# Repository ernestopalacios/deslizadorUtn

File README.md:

DeslizadorUtn
=============

Repositorio para el deslizador lineal desarrollado para la Universidad Técnica del Norte.

Manual de ayuda: https://github.com/ernestopalacios/deslizadorUtn/wiki

El reposito esta dividido en las siguientes carpetas:

---> deslizador :  Archivos del deslizador en SolidWorks 2013

---> deslizadorlineal : Documentación del trabajo de grado.

---> labview : Libreria para el control del servomotor en LABVIEW.

---> mbed : Documentacion microcontrolador.

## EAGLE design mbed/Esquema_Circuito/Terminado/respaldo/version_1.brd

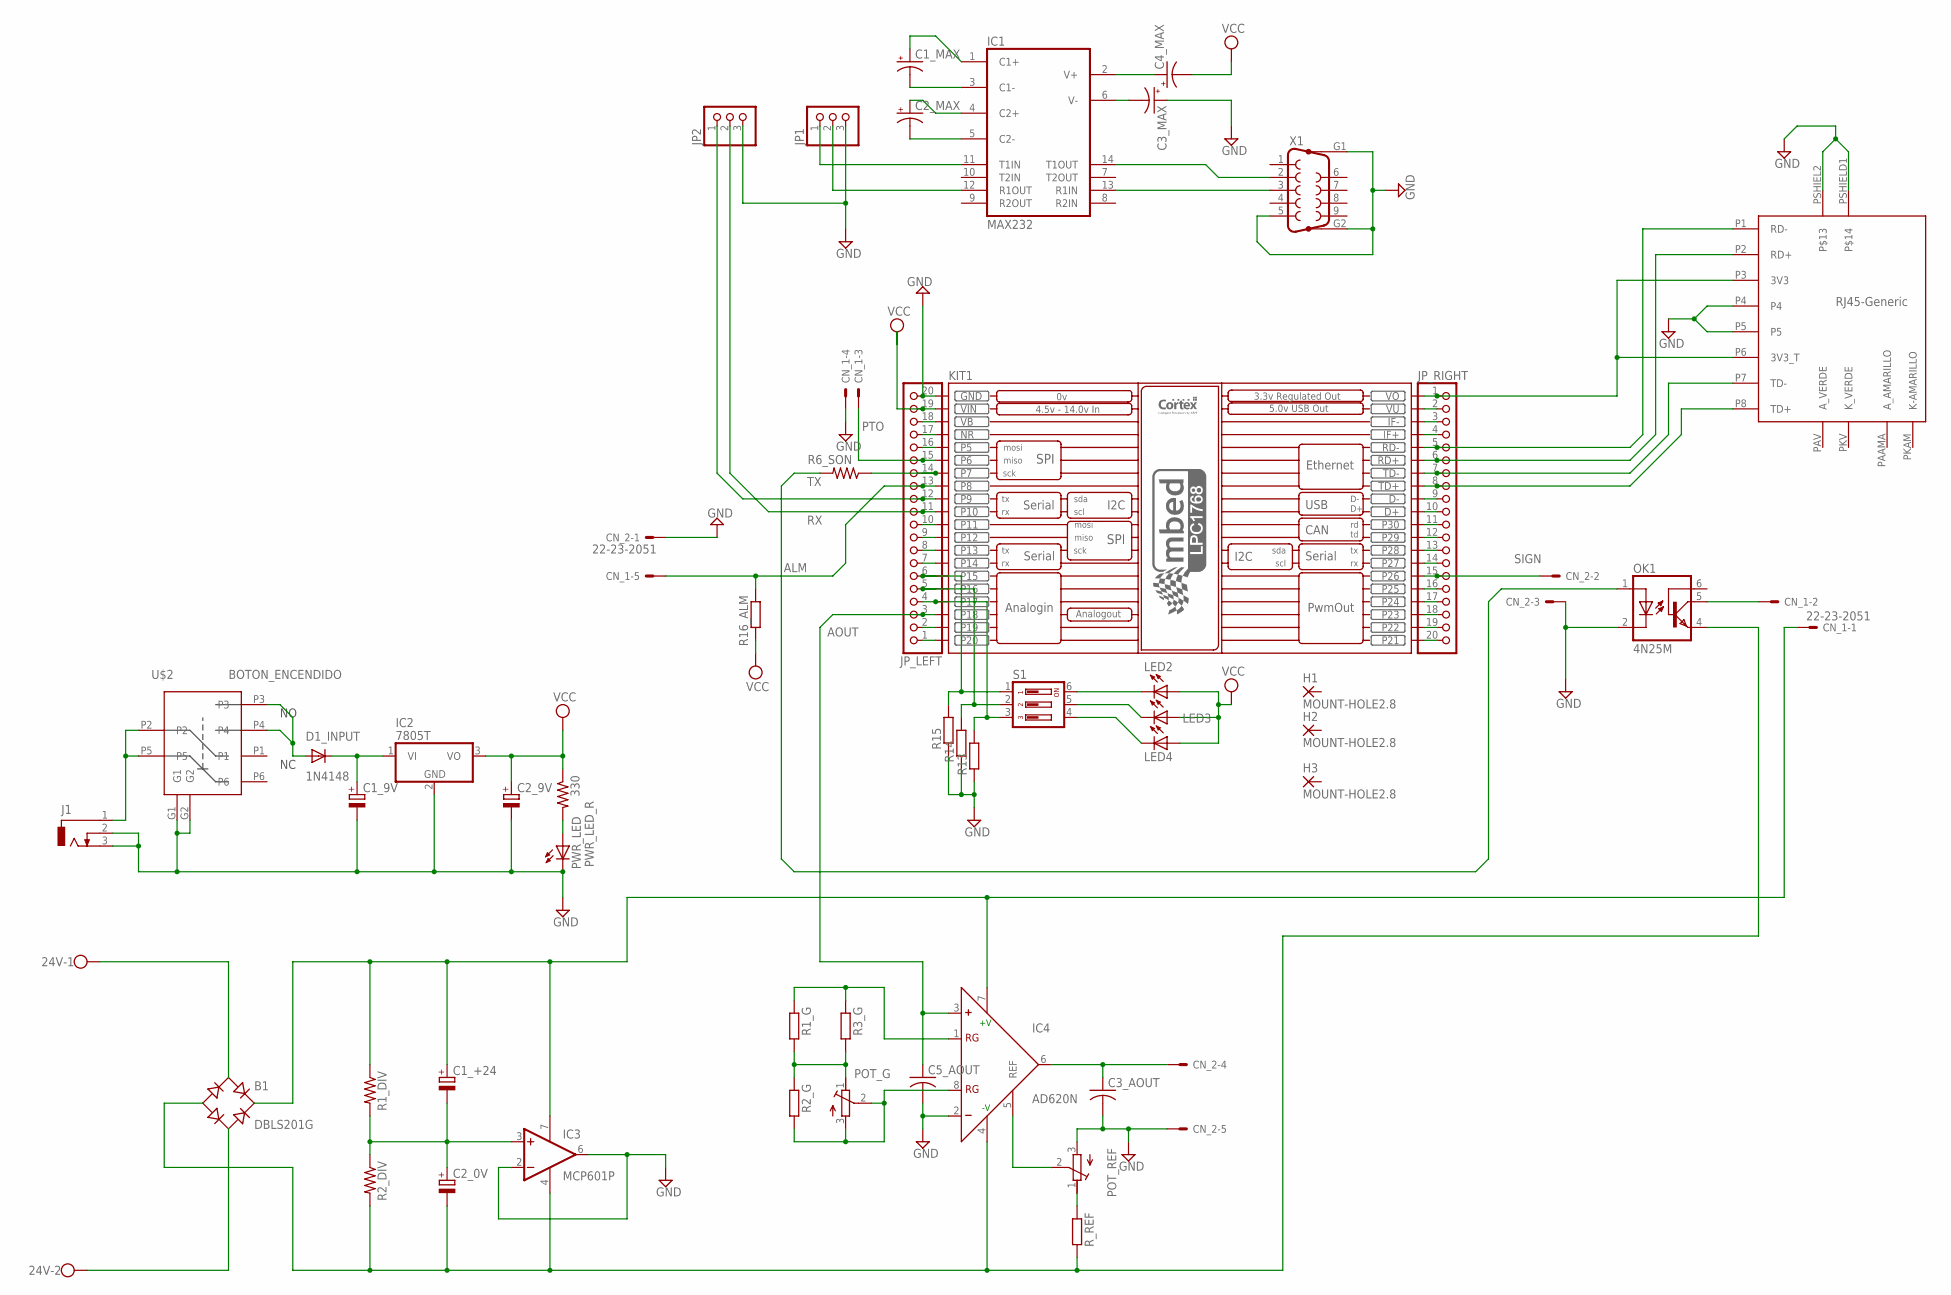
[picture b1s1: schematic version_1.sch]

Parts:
24V: W237-02P; W237-132
B1: DBLS201G; DBS
C1_9V, C1_+24, C2_0V, C2_9V: CPOL-EUTT5D7; TT5D7
C1_MAX, C2_MAX, C3_MAX, C4_MAX: CPOL-USE2,5-6E; E2,5-6E
C3_AOUT, C5_AOUT: C-US025-024X044; C025-024X044
CN_1, CN_2: 22-23-2051
D1_INPUT: 1N4148; DO35-10
H1, H2, H3: MOUNT-HOLE2.8; 2,54/0,8
IC1: MAX232; DIL16
IC2: 7805T; TO220H
IC3: MCP601P; DIL08
IC4: AD620N; DIL08
J1: DCJ0303
JP1, JP2: PINHD-1X3; 1X03
JP_LEFT: PINHD-1X20; 1X20
JP_RIGHT: PINHD-1X20; 1X20
KIT1: MBED_NXP_LPC1768; MBED-KIT
LED2, LED3, LED4: LED3MM
OK1: 4N25M; DIL06
POT_G: R-TRIMMT93XB; RTRIMT93XB
POT_REF: R-TRIMMT93XB; RTRIMT93XB
PWR_LED: LED3MM
PWR_LED_R: 330; 0207/15
R1_DIV, R2_DIV: R-US_0207/10; 0207/10
R1_G, R2_G, R3_G: R-EU_0207/2V; 0207/2V
R6_SON: R-US_0207/7; 0207/7
R13, R14, R15: R-EU_0207/15; 0207/15
R16_ALM: R-EU_0207/12; 0207/12
R_REF: R-EU_0207/2V; 0207/2V
S1: DIP03YL
U$1: RJ-45-GENERIC; RJ45-GENERIC
U$2: BOTON_ENCENDIDO; BOTON_ENCNEDIDO
X1: F09HP

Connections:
ALM: CN_1.5, JP_LEFT.13, KIT1.P$8 (P8), R16_ALM.1
AOUT: C5_AOUT.1, IC4.3 (+), JP_LEFT.3, KIT1.P$18 (P18)
GND: C1_9V.-, C2_9V.-, C3_AOUT.2, C3_MAX.+, C5_AOUT.2, CN_1.4, CN_2.1, CN_2.3, CN_2.5, IC1.15 (GND), IC2.2 (GND), IC3.2 (-IN), IC3.6 (OUT), IC4.2 (-), J1.2, J1.3, JP1.3, JP2.3, JP_LEFT.20, KIT1.GND, OK1.2 (C), POT_REF.3 (E), PWR_LED.K (C), R13.1, R14.1, R15.1, U$1.P4, U$1.P5, U$1.PSHIEL2, U$1.PSHIELD1, U$2.G1, U$2.G2, X1.5, X1.G1, X1.G2
unnamed: B1.+, C1_+24.+, CN_1.1, IC3.7 (V+), IC4.7 (+V), R1_DIV.1
unnamed: B1.-, C2_0V.-, IC3.4 (V-), IC4.4 (-V), OK1.4 (EMI), R2_DIV.2, R_REF.2
unnamed: C1_+24.-, C2_0V.+, IC3.3 (+IN), R1_DIV.2, R2_DIV.1
unnamed: CN_1.2, OK1.5 (COL)
unnamed: JP_RIGHT.2, KIT1.VU
unnamed: C3_AOUT.1, CN_2.4, IC4.6 (OUT)
unnamed: JP_RIGHT.3, KIT1.IF-
unnamed: POT_REF.1 (A), R_REF.1
unnamed: IC4.1 (RG), R1_G.1, R3_G.1
unnamed: POT_G.1 (A), R1_G.2, R2_G.1, R3_G.2
unnamed: IC4.8 (RG), POT_G.2 (S), POT_G.3 (E), R2_G.2
unnamed: D1_INPUT.A, U$2.P3, U$2.P4
unnamed: JP_LEFT.5, KIT1.P$16 (P16), R14.2, S1.2
unnamed: JP_RIGHT.4, KIT1.IF+
unnamed: IC4.5 (REF), POT_REF.2 (S)
unnamed: JP_RIGHT.11, KIT1.P$30 (P30)
unnamed: OK1.1 (A), R6_SON.2
unnamed: J1.1, U$2.P2, U$2.P5
unnamed: JP_LEFT.4, KIT1.P$17 (P17), R13.2, S1.3
unnamed: JP_RIGHT.1, KIT1.VOUT (VO), U$1.P3 (3V3), U$1.P6 (3V3_T)
unnamed: C1_9V.+, D1_INPUT.C, IC2.1 (VI)
unnamed: IC1.11 (T1IN), JP1.1
unnamed: IC1.12 (R1OUT), JP1.2
unnamed: LED2.K (C), S1.6
unnamed: LED3.K (C), S1.5
unnamed: LED4.K (C), S1.4
unnamed: JP_RIGHT.5, KIT1.RD-, U$1.P1 (RD-)
unnamed: JP_RIGHT.6, KIT1.RD+, U$1.P2 (RD+)
unnamed: JP_RIGHT.7, KIT1.TD-, U$1.P7 (TD-)
unnamed: JP_RIGHT.8, KIT1.TD+, U$1.P8 (TD+)
unnamed: JP_RIGHT.9, KIT1.D-
unnamed: JP_RIGHT.10, KIT1.D+
unnamed: C1_MAX.+, IC1.1 (C1+)
unnamed: C1_MAX.-, IC1.3 (C1-)
unnamed: C2_MAX.-, IC1.5 (C2-)
unnamed: C2_MAX.+, IC1.4 (C2+)
unnamed: C4_MAX.+, IC1.2 (V+)
unnamed: C3_MAX.-, IC1.6 (V-)
unnamed: JP_RIGHT.13, KIT1.P$28 (P28)
unnamed: IC1.14 (T1OUT), X1.2
unnamed: IC1.13 (R1IN), X1.3
unnamed: JP_RIGHT.18, KIT1.P$23 (P23)
unnamed: JP_RIGHT.19, KIT1.P$22 (P22)
unnamed: JP_RIGHT.14, KIT1.P$27 (P27)
unnamed: JP_RIGHT.16, KIT1.P$25 (P25)
unnamed: JP_RIGHT.17, KIT1.P$24 (P24)
unnamed: JP_LEFT.18, KIT1.VB
unnamed: JP_LEFT.17, KIT1.NR
unnamed: JP_LEFT.16, KIT1.P$5 (P5)
unnamed: JP_LEFT.14, KIT1.P$7 (P7), R6_SON.1
unnamed: JP_LEFT.10, KIT1.P$11 (P11)
unnamed: JP_LEFT.9, KIT1.P$12 (P12)
unnamed: JP_LEFT.8, KIT1.P$13 (P13)
unnamed: JP_LEFT.6, KIT1.P$15 (P15), R15.2, S1.1
unnamed: JP_LEFT.7, KIT1.P$14 (P14)
unnamed: JP_LEFT.2, KIT1.P$19 (P19)
unnamed: JP_LEFT.1, KIT1.P$20 (P20)
unnamed: PWR_LED.A, PWR_LED_R.2
unnamed: JP_RIGHT.20, KIT1.P$21 (P21)
unnamed: 24V.1, B1.AC1
unnamed: 24V.2, B1.AC2
PTO: CN_1.3, JP_LEFT.15, KIT1.P$6 (P6)
RX: JP2.2, JP_LEFT.11, KIT1.P$10 (P10)
SIGN: CN_2.2, JP_RIGHT.15, KIT1.P$26 (P26)
SIGN+: JP_RIGHT.12, KIT1.P$29 (P29)
TX: JP2.1, JP_LEFT.12, KIT1.P$9 (P9)
VCC: C2_9V.+, C4_MAX.-, IC1.16 (VCC), IC2.3 (VO), JP_LEFT.19, KIT1.VIN, LED2.A, LED3.A, LED4.A, PWR_LED_R.1, R16_ALM.2

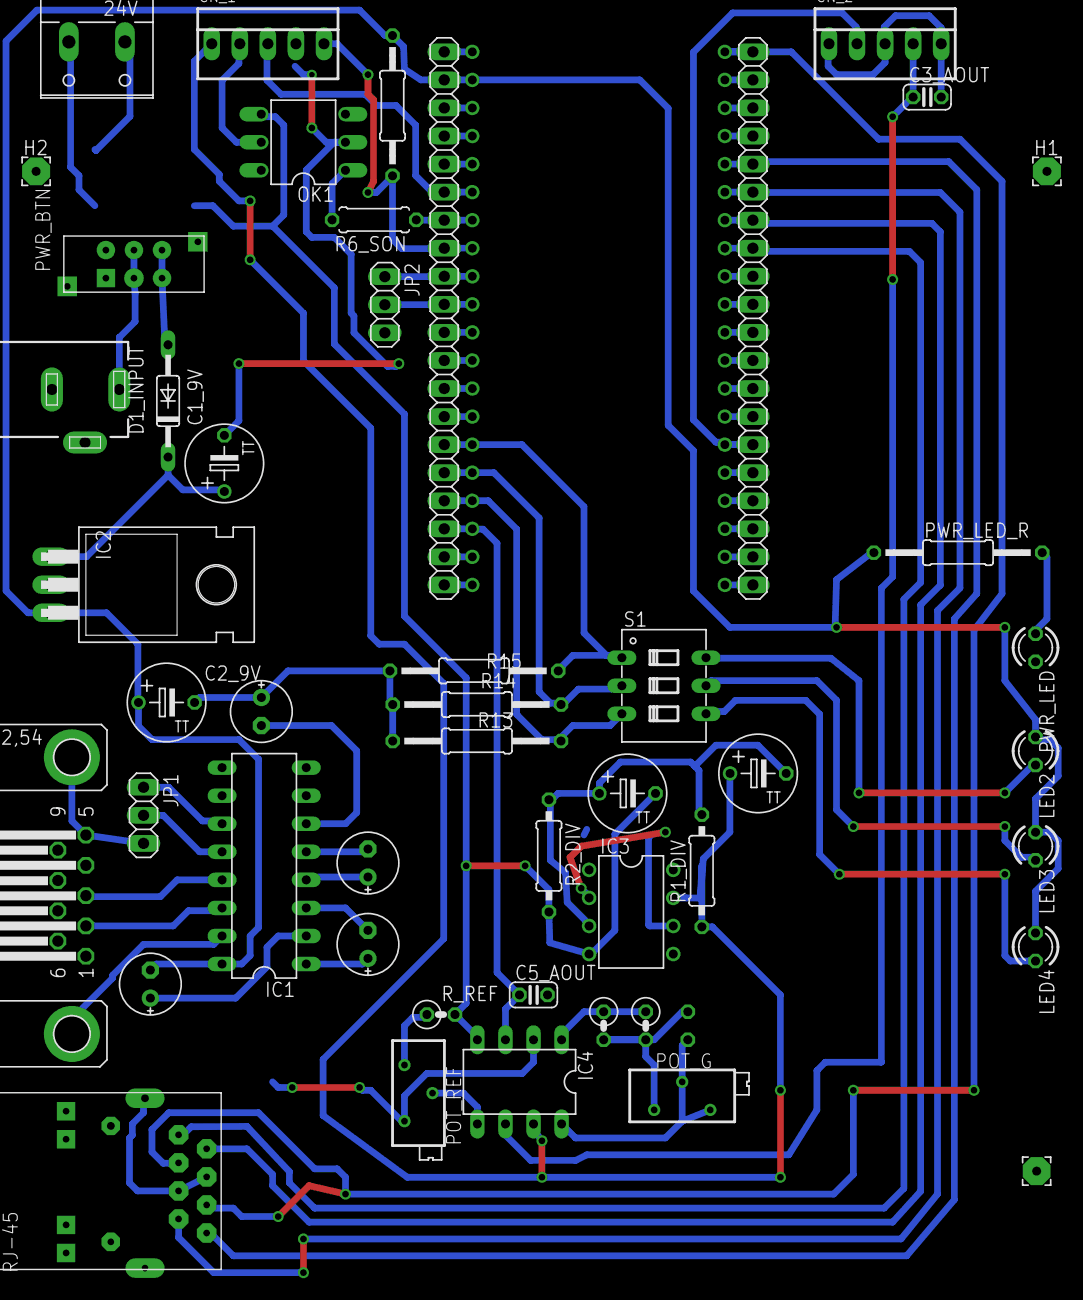
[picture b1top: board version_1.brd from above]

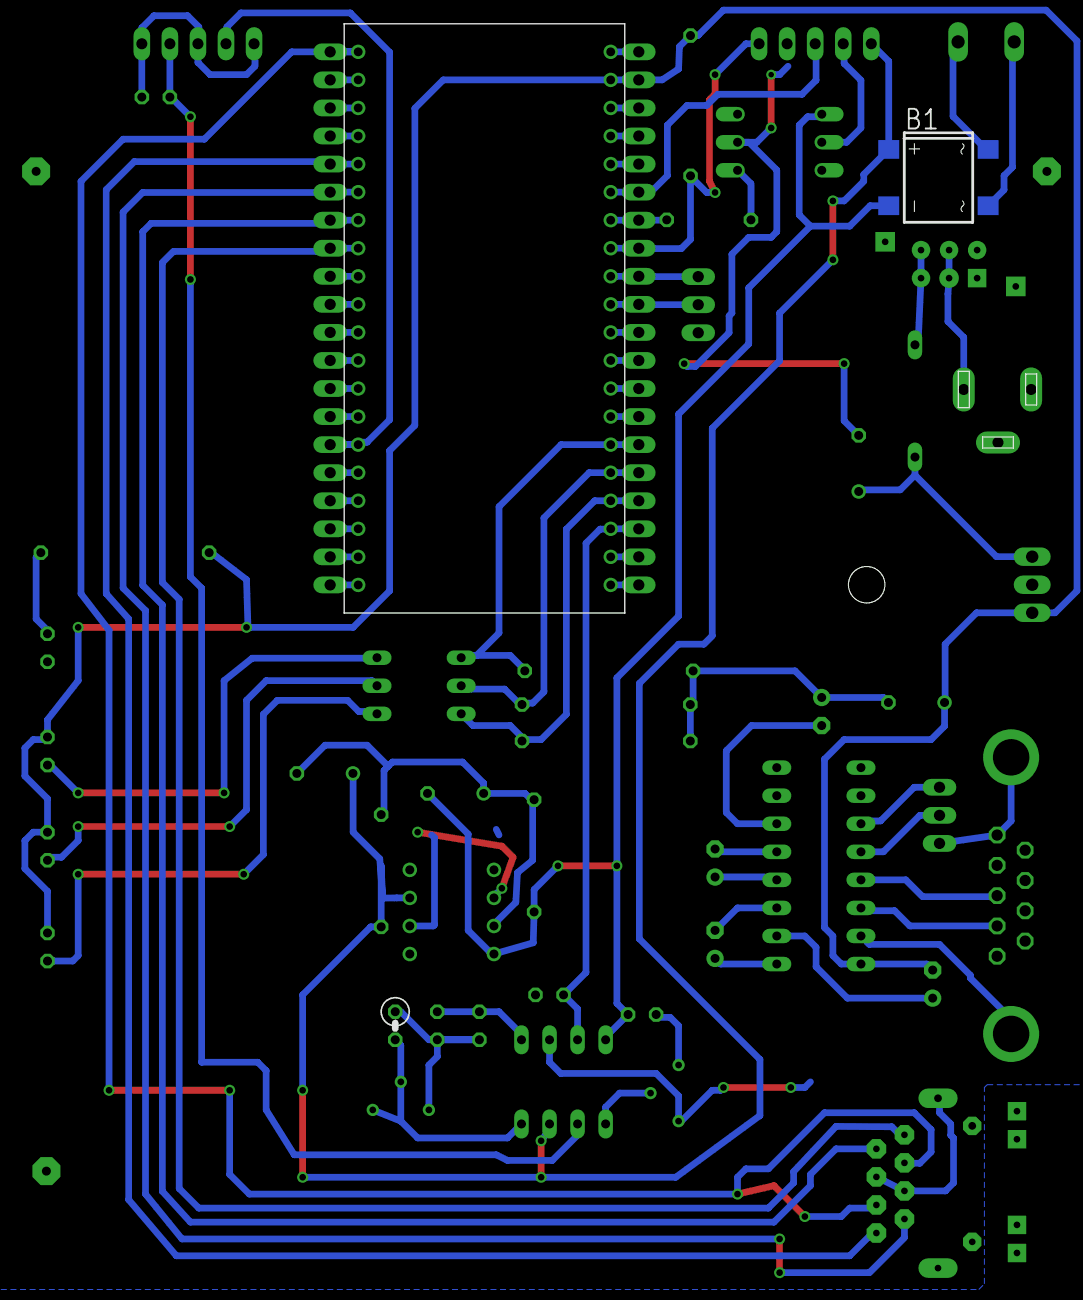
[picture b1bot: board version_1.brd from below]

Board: 2 copper layers, 51 parts (2 on the bottom side), 70 nets.

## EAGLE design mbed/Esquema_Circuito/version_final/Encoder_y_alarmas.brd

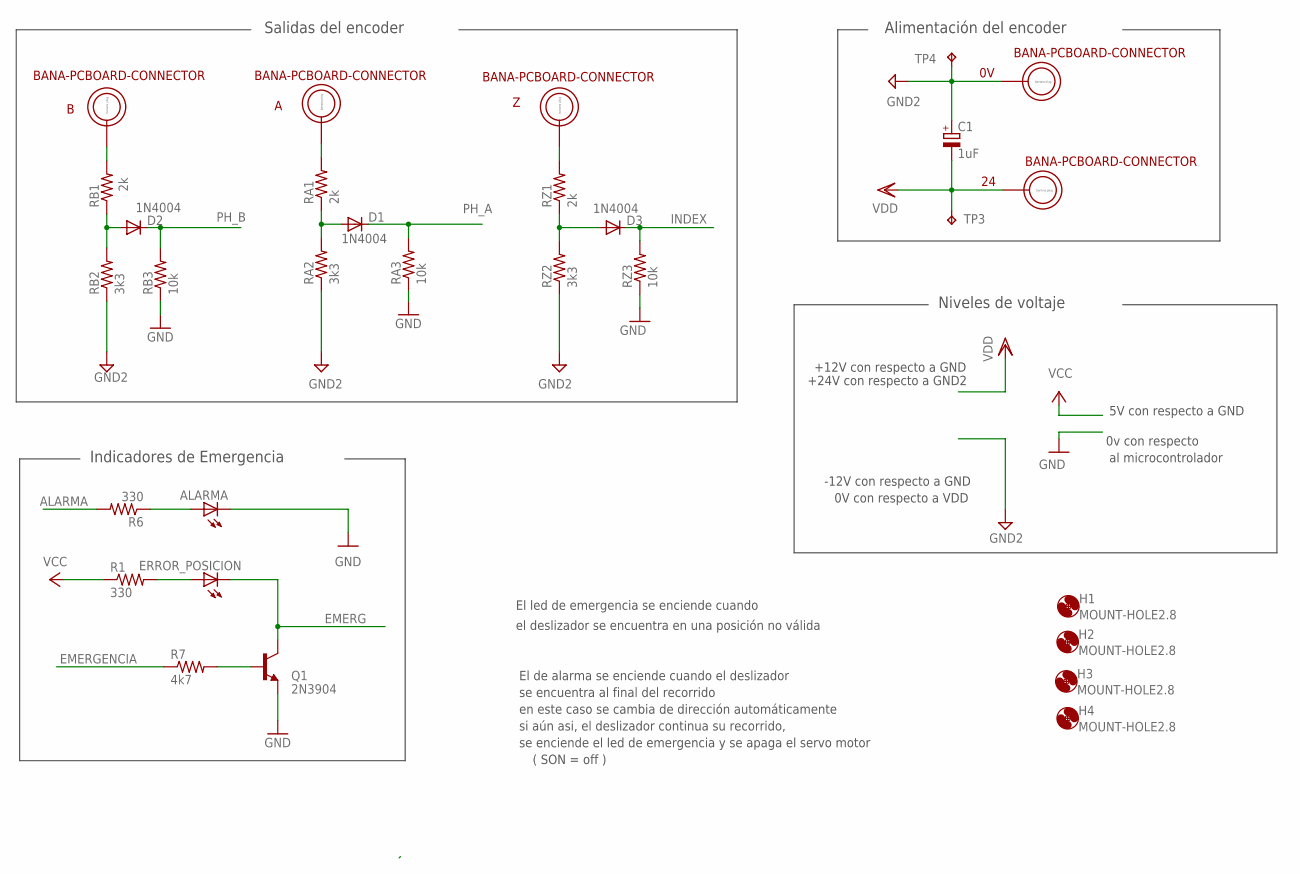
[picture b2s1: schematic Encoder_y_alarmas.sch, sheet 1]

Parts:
0V, 24: BANA-PCBOARD-CONNECTOR; BANA_PLUG
A: BANA-PCBOARD-CONNECTOR; BANA_PLUG
ALARMA: LED5MM
B: BANA-PCBOARD-CONNECTOR; BANA_PLUG
C1: 1uF; E2,5-6
D1, D2, D3: 1N4004; DO41-10
ERROR_POSICION: LED5MM
H1, H2, H3, H4: MOUNT-HOLE2.8; 2,8
Q1: 2N3904; TO92
R1, R6: 330; 0204/7
R7: 4k7; 0204/7
RA1: 2k; 0204/7
RA2: 3k3; 0204/7
RA3: 10k; 0204/7
RB1: 2k; 0204/7
RB2: 3k3; 0204/7
RB3: 10k; 0204/7
RZ1: 2k; 0204/7
RZ2: 3k3; 0204/7
RZ3: 10k; 0204/7
TP3, TP4: TPB2,54; B2,54
Z: BANA-PCBOARD-CONNECTOR; BANA_PLUG

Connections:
ALARMA: R6.2; also elsewhere on the board
EMERG: ERROR_POSICION.K (C), Q1.1 (C); also elsewhere on the board
EMERGENCIA: R7.1; also elsewhere on the board
GND: ALARMA.K (C), Q1.3 (E), RA3.1, RB3.1, RZ3.1; also elsewhere on the board
GND2: 0V.P$1, C1.+, RA2.1, RB2.1, RZ2.1, TP4.TP; also elsewhere on the board
INDEX: D3.C, RZ3.2; also elsewhere on the board
unnamed: Q1.2 (B), R7.2
unnamed: ERROR_POSICION.A, R1.2
unnamed: ALARMA.A, R6.1
unnamed: D1.A, RA1.1, RA2.2
unnamed: D2.A, RB1.1, RB2.2
unnamed: RZ1.2, Z.P$1
unnamed: B.P$1, RB1.2
unnamed: A.P$1, RA1.2
unnamed: D3.A, RZ1.1, RZ2.2
PH_A: D1.C, RA3.2; also elsewhere on the board
PH_B: D2.C, RB3.2; also elsewhere on the board
VCC: R1.1; also elsewhere on the board
VDD: 24.P$1, C1.-, TP3.TP; also elsewhere on the board

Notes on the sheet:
0v con respecto
5V con respecto a GND
+12V con respecto a GND
+24V con respecto a GND2
-12V con respecto a GND
0V con respecto a VDD
El led de emergencia se enciende cuando
el deslizador se encuentra en una posición no válida
El de alarma se enciende cuando el deslizador
se encuentra al final del recorrido
en este caso se cambia de dirección automáticamente
si aún asi, el deslizador continua su recorrido,
se enciende el led de emergencia y se apaga el servo motor
( SON = off )
Indicadores de Emergencia
Salidas del encoder
Alimentación del encoder
Niveles de voltaje
al microcontrolador

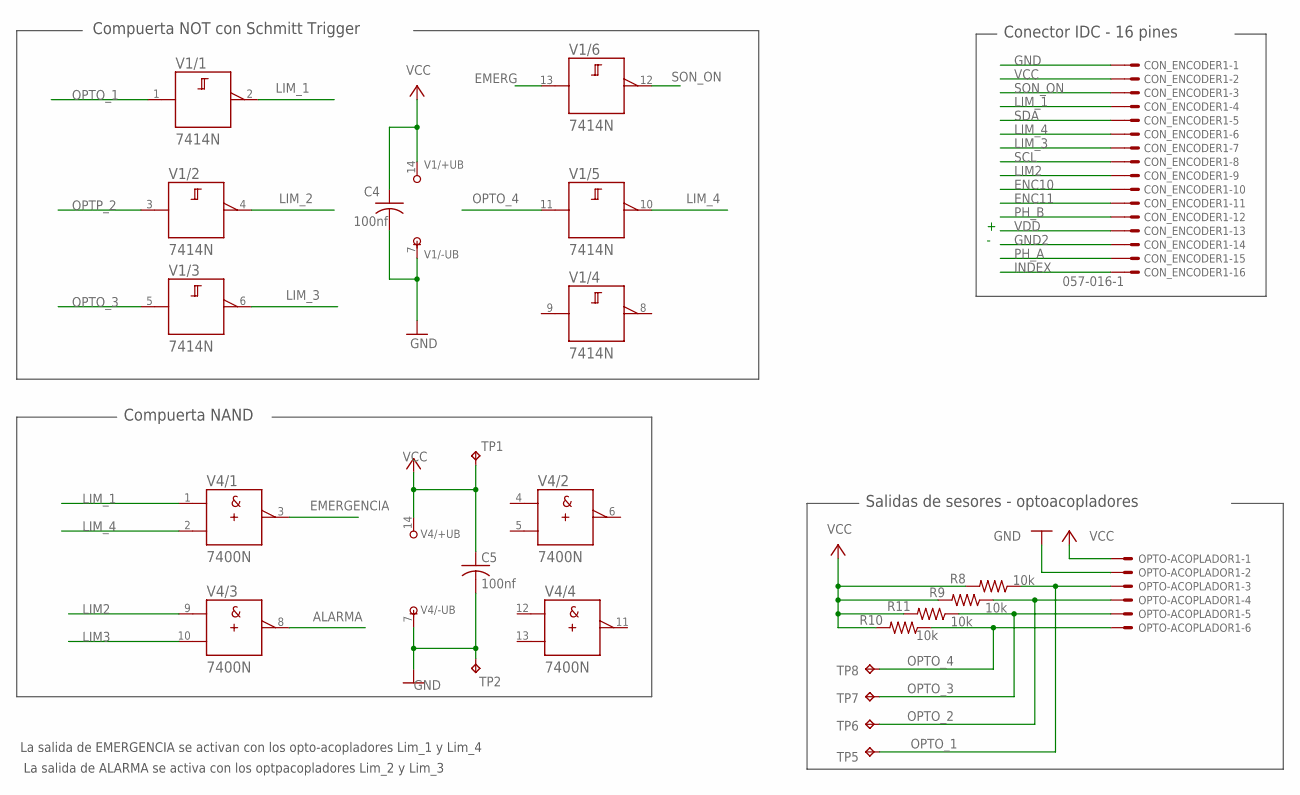
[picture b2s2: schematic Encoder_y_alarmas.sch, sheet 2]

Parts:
C4, C5: 100nf; C025-024X044
CON_ENCODER1: 057-016-1
OPTO-ACOPLADOR1: 22-23-2061
R8, R9, R10, R11: 10k; 0204/7
TP1, TP2, TP5, TP6, TP7, TP8: TPB2,54; B2,54
V1: 7414N; DIL14
V4: 7400N; DIL14

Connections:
ALARMA: V4.8 (Y); also elsewhere on the board
EMERG: V1.13 (A); also elsewhere on the board
EMERGENCIA: V4.3 (Y); also elsewhere on the board
ENC10: CON_ENCODER1.10
ENC11: CON_ENCODER1.11
GND: C4.2, C5.2, CON_ENCODER1.1, OPTO-ACOPLADOR1.2, TP2.TP, V1.7 (-UB), V4.7 (-UB); also elsewhere on the board
GND2: CON_ENCODER1.14; also elsewhere on the board
INDEX: CON_ENCODER1.16; also elsewhere on the board
LIM2: CON_ENCODER1.9, V4.9 (A)
LIM3: V4.10 (B)
LIM_1: CON_ENCODER1.4, V1.2 (Y), V4.1 (A)
LIM_2: V1.4 (Y)
LIM_3: CON_ENCODER1.7, V1.6 (Y)
LIM_4: CON_ENCODER1.6, V1.10 (Y), V4.2 (B)
OPTO_1: OPTO-ACOPLADOR1.3, R8.1, TP5.TP, V1.1 (A)
OPTO_2: OPTO-ACOPLADOR1.4, R9.1, TP6.TP
OPTO_3: OPTO-ACOPLADOR1.5, R11.1, TP7.TP, V1.5 (A)
OPTO_4: OPTO-ACOPLADOR1.6, R10.1, TP8.TP, V1.11 (A)
OPTP_2: V1.3 (A)
PH_A: CON_ENCODER1.15; also elsewhere on the board
PH_B: CON_ENCODER1.12; also elsewhere on the board
SCL: CON_ENCODER1.8
SDA: CON_ENCODER1.5
SON_ON: CON_ENCODER1.3, V1.12 (Y)
VCC: C4.1, C5.1, CON_ENCODER1.2, OPTO-ACOPLADOR1.1, R8.2, R9.2, R10.2, R11.2, TP1.TP, V1.14 (+UB), V4.14 (+UB); also elsewhere on the board
VDD: CON_ENCODER1.13; also elsewhere on the board

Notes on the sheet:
Compuerta NAND
Compuerta NOT con Schmitt Trigger
Conector IDC - 16 pines
Salidas de sesores - optoacopladores
La salida de EMERGENCIA se activan con los opto-acopladores Lim_1 y Lim_4
La salida de ALARMA se activa con los optpacopladores Lim_2 y Lim_3

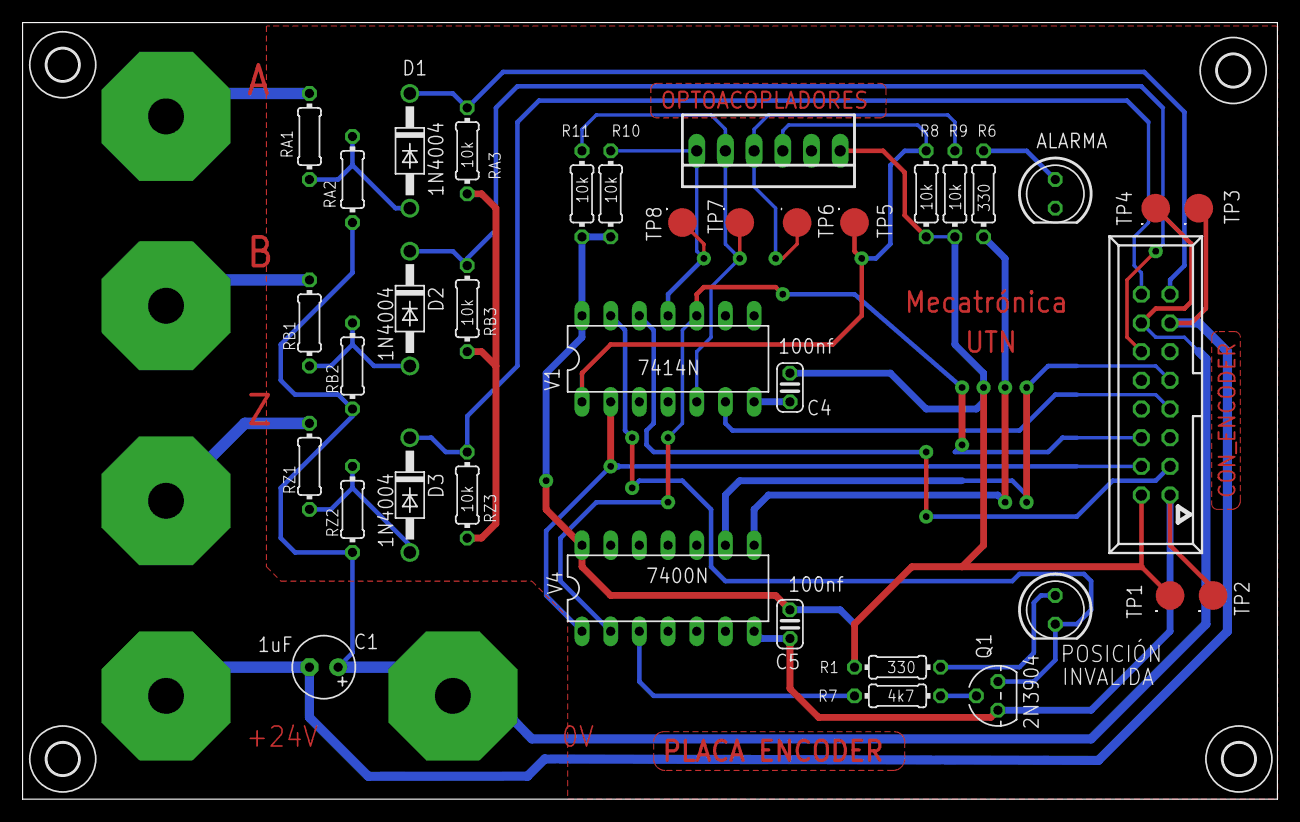
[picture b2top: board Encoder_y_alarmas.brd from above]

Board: 2 copper layers, 111.1 x 68.8 mm, 46 parts (0 on the bottom side), 28 nets.

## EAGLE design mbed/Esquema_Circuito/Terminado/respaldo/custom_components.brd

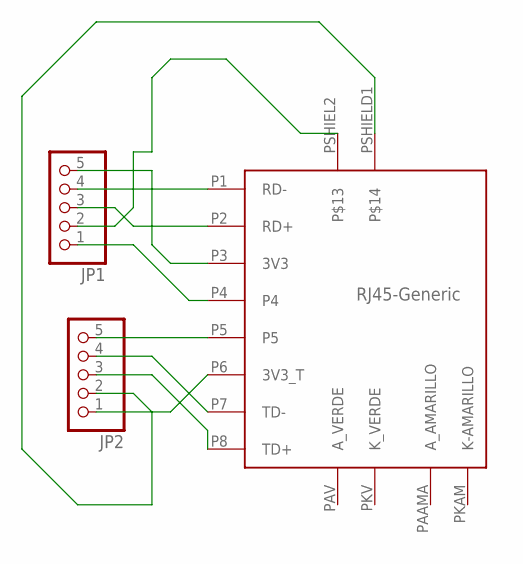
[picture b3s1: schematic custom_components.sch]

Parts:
JP1, JP2: PINHD-1X5; 1X05
U$2: RJ-45-GENERIC; RJ45-GENERIC

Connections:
unnamed: JP1.5, U$2.P3 (3V3)
unnamed: JP1.4, U$2.P1 (RD-)
unnamed: JP1.3, U$2.P2 (RD+)
unnamed: JP1.2, U$2.PSHIEL2
unnamed: JP1.1, U$2.P4
unnamed: JP2.5, U$2.P5
unnamed: JP2.4, U$2.P7 (TD-)
unnamed: JP2.3, U$2.P8 (TD+)
unnamed: JP2.2, U$2.PSHIELD1
unnamed: JP2.1, U$2.P6 (3V3_T)

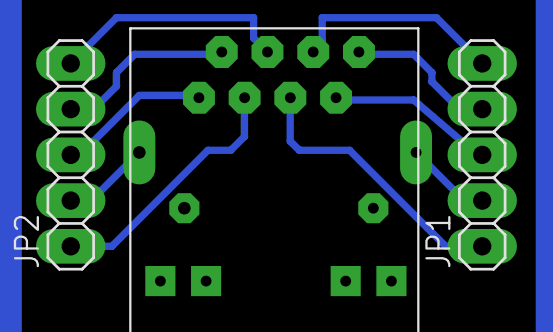
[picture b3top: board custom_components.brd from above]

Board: 2 copper layers, 3 parts (0 on the bottom side), 10 nets.

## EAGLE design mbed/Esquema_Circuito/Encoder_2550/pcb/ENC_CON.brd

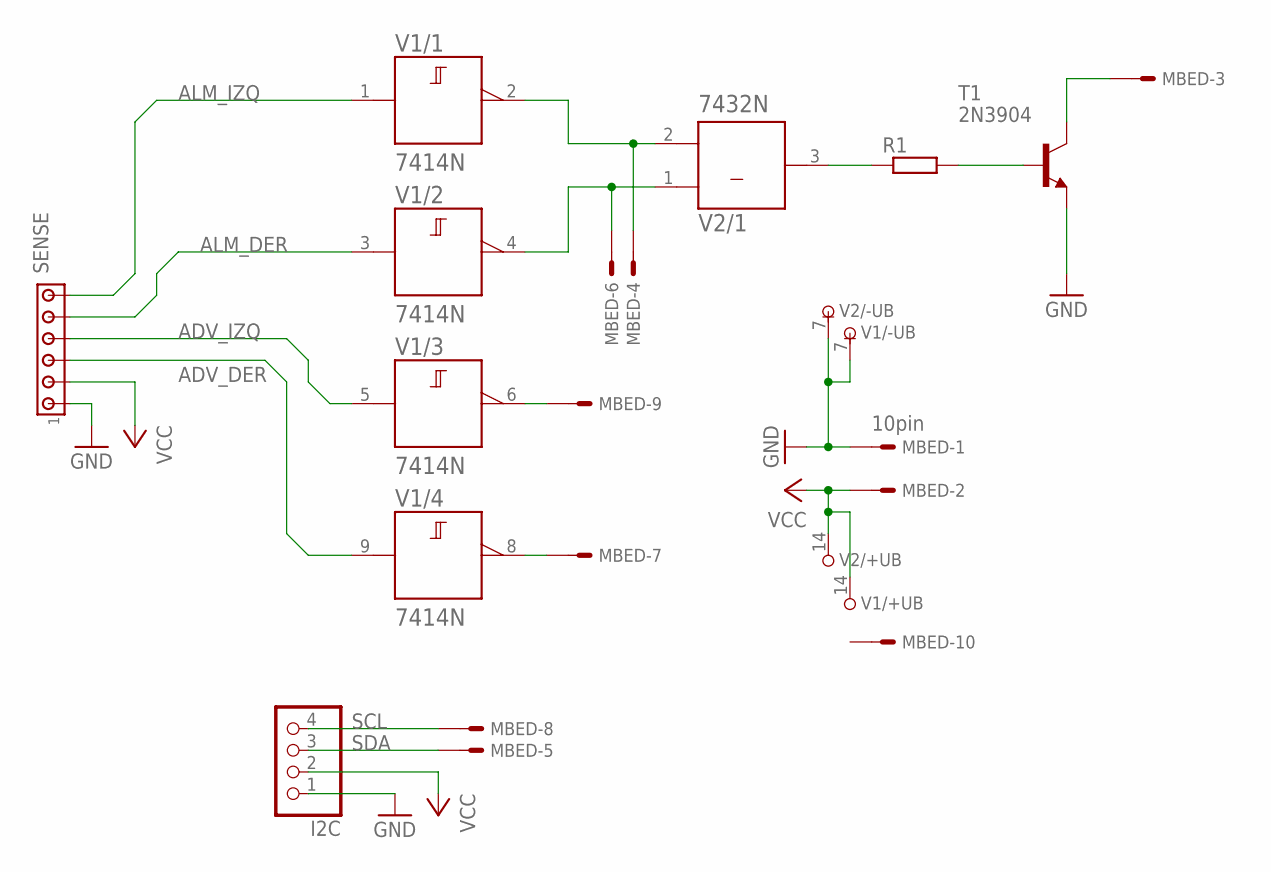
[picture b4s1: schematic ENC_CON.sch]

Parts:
I2C: PINHD-1X4/90; 1X04/90
MBED: 10pin; 057-010-1
R1: R-EU_0207/10; 0207/10
SENSE: MTA06-100; 10X06MTA
T1: 2N3904; TO92
V1: 7414N; DIL14
V2: 7432N; DIL14

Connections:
ADV_DER: SENSE.4 (3), V1.9 (A)
ADV_IZQ: SENSE.3 (4), V1.5 (A)
ALM_DER: SENSE.2 (5), V1.3 (A)
ALM_IZQ: SENSE.1 (6), V1.1 (A)
GND: I2C.1, MBED.1, SENSE.6 (1), T1.3 (E), V1.7 (-UB), V2.7 (-UB)
unnamed: MBED.9, V1.6 (Y)
unnamed: MBED.7, V1.8 (Y)
unnamed: R1.1, V2.3 (Y)
unnamed: MBED.4, V1.2 (Y), V2.2 (B)
unnamed: MBED.6, V1.4 (Y), V2.1 (A)
unnamed: R1.2, T1.2 (B)
unnamed: MBED.3, T1.1 (C)
SCL: I2C.4, MBED.8
SDA: I2C.3, MBED.5
VCC: I2C.2, MBED.2, SENSE.5 (2), V1.14 (+UB), V2.14 (+UB)

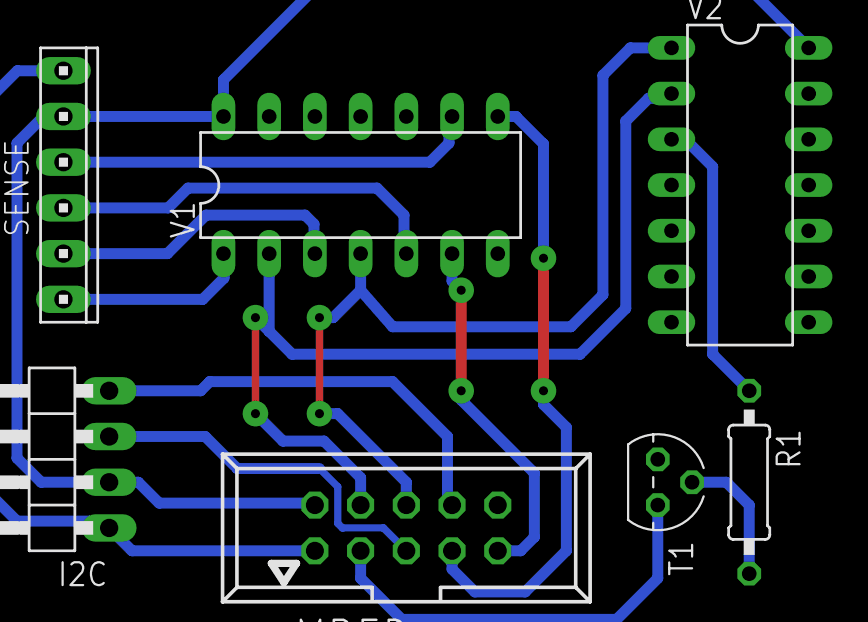
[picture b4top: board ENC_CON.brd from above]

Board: 2 copper layers, 7 parts (0 on the bottom side), 15 nets.

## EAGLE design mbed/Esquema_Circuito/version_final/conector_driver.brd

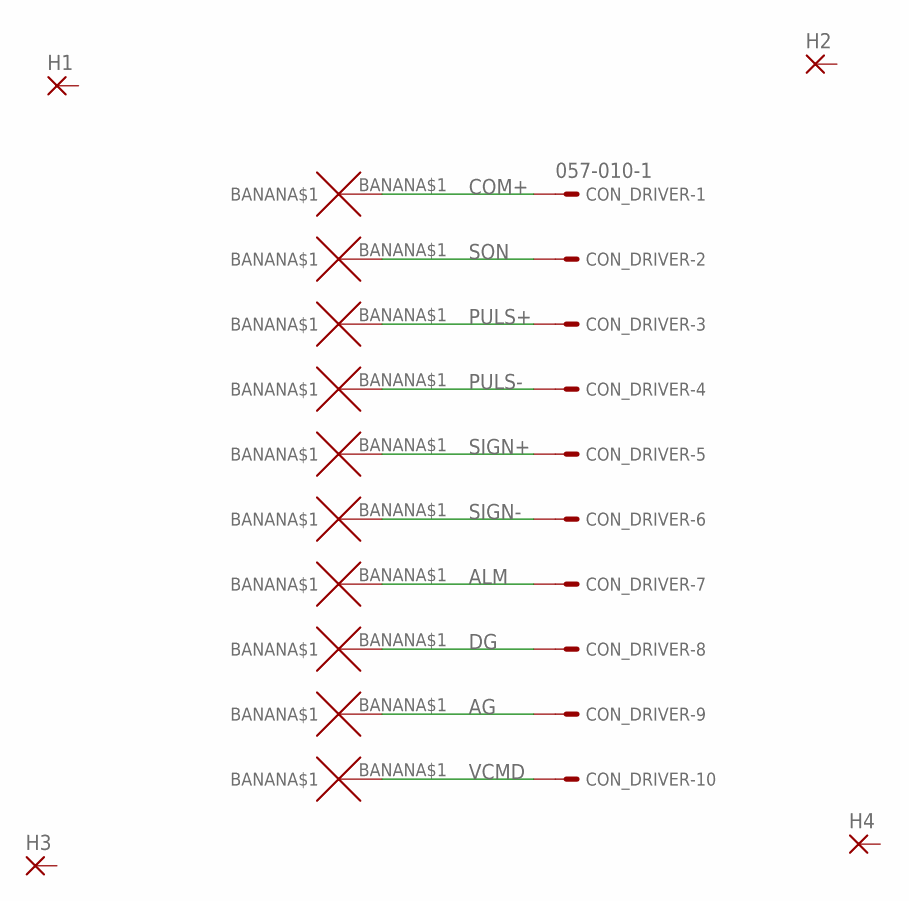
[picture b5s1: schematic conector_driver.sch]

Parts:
AG: BANANA
ALM: BANANA
COM+: BANANA
CON_DRIVER: 057-010-1
DG: BANANA
H1, H2, H3, H4: 3,81/1,4
PULS+: BANANA
PULS-: BANANA
SIGN+: BANANA
SIGN-: BANANA
SON: BANANA
VCMD: BANANA

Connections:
AG: AG.BANANA$1, CON_DRIVER.9
ALM: ALM.BANANA$1, CON_DRIVER.7
COM+: COM+.BANANA$1, CON_DRIVER.1
DG: CON_DRIVER.8, DG.BANANA$1
PULS+: CON_DRIVER.3, PULS+.BANANA$1
PULS-: CON_DRIVER.4, PULS-.BANANA$1
SIGN+: CON_DRIVER.5, SIGN+.BANANA$1
SIGN-: CON_DRIVER.6, SIGN-.BANANA$1
SON: CON_DRIVER.2, SON.BANANA$1
VCMD: CON_DRIVER.10, VCMD.BANANA$1

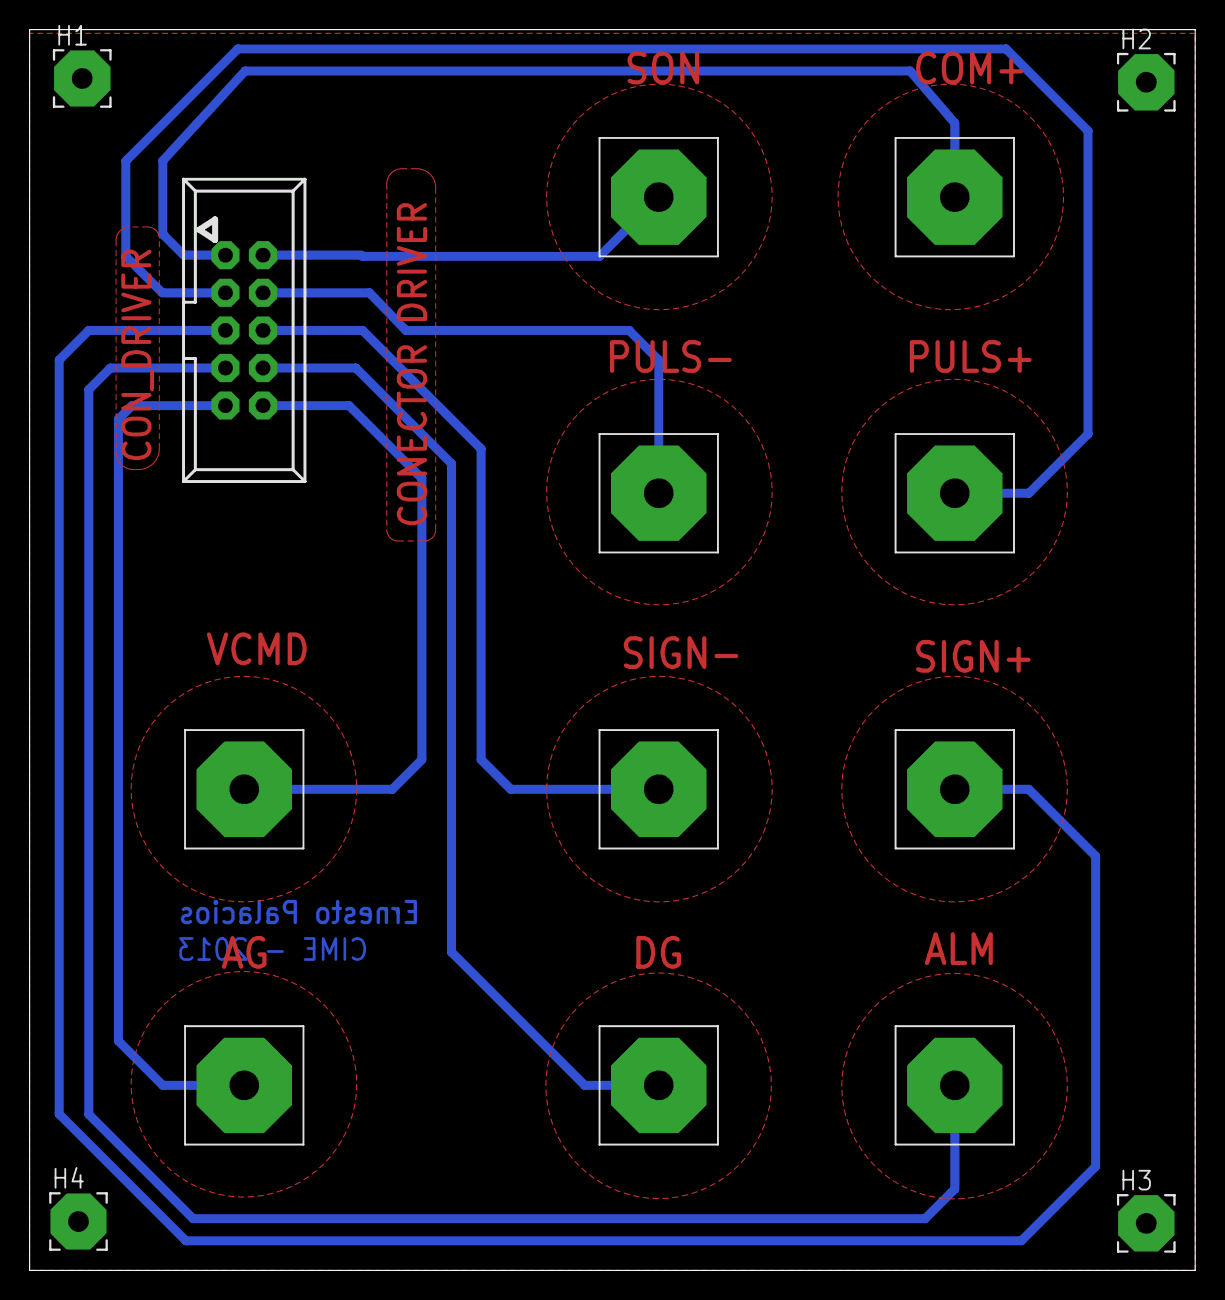
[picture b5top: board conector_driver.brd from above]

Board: 2 copper layers, 78.7 x 83.8 mm, 15 parts (0 on the bottom side), 10 nets.

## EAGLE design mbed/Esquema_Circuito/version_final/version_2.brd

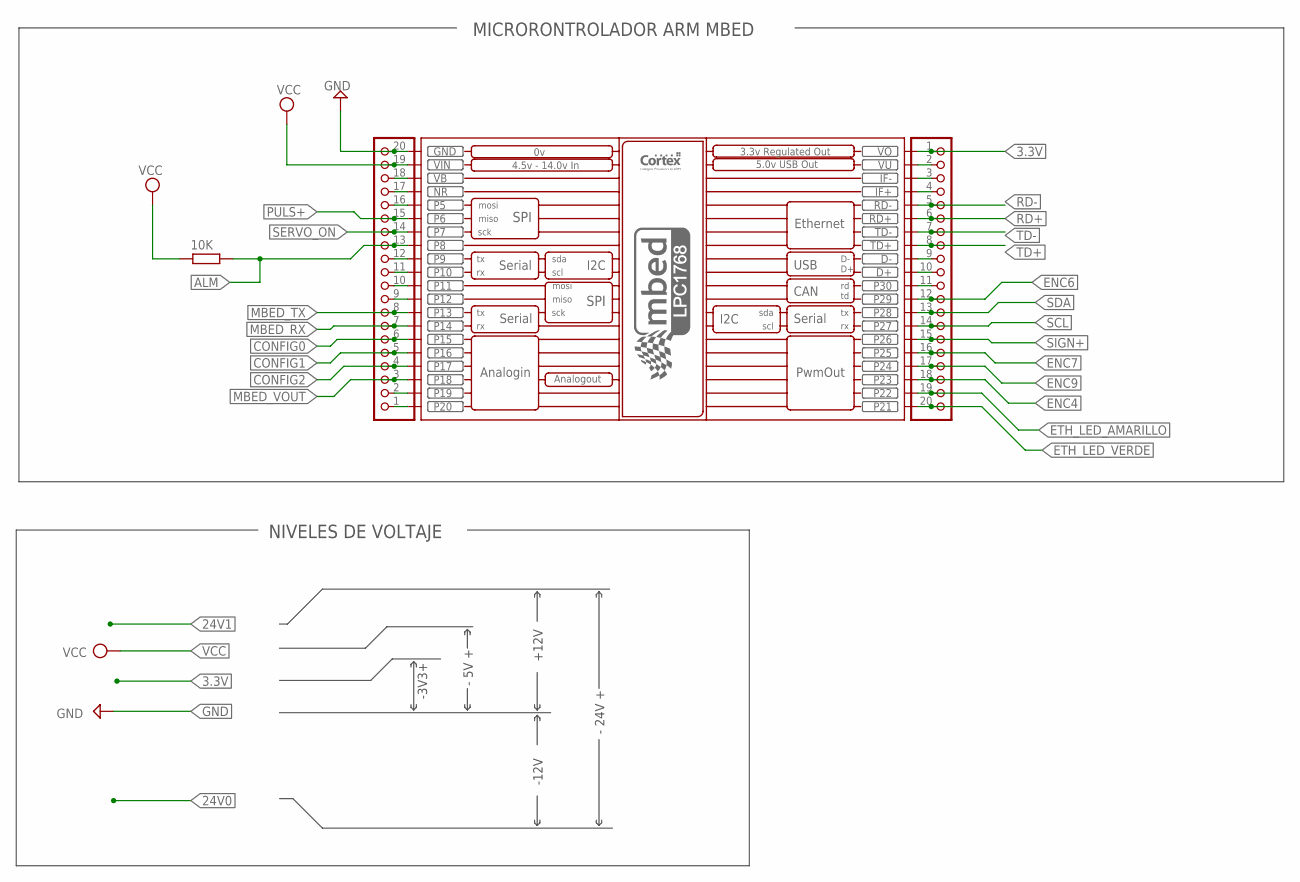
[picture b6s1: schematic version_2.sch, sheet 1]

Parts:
JP_LEFT: PINHD-1X20; 1X20
JP_RIGHT: PINHD-1X20; 1X20
KIT1: MBED_NXP_LPC1768; MBED-KIT
R16_ALM: 10K; 0207/12

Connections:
3.3V: JP_RIGHT.1, KIT1.VOUT (VO); also elsewhere on the board
ALM: JP_LEFT.13, KIT1.P$8 (P8), R16_ALM.1; also elsewhere on the board
CONFIG0: JP_LEFT.6, KIT1.P$15 (P15); also elsewhere on the board
CONFIG1: JP_LEFT.5, KIT1.P$16 (P16); also elsewhere on the board
CONFIG2: JP_LEFT.4, KIT1.P$17 (P17); also elsewhere on the board
ENC4: JP_RIGHT.18, KIT1.P$23 (P23); also elsewhere on the board
ENC6: JP_RIGHT.12, KIT1.P$29 (P29); also elsewhere on the board
ENC7: JP_RIGHT.16, KIT1.P$25 (P25); also elsewhere on the board
ENC9: JP_RIGHT.17, KIT1.P$24 (P24); also elsewhere on the board
ETH_LED_AMARILLO: JP_RIGHT.19, KIT1.P$22 (P22); also elsewhere on the board
ETH_LED_VERDE: JP_RIGHT.20, KIT1.P$21 (P21); also elsewhere on the board
GND: JP_LEFT.20, KIT1.GND; also elsewhere on the board
MBED_RX: JP_LEFT.7, KIT1.P$14 (P14); also elsewhere on the board
MBED_TX: JP_LEFT.8, KIT1.P$13 (P13); also elsewhere on the board
MBED_VOUT: JP_LEFT.3, KIT1.P$18 (P18); also elsewhere on the board
unnamed: JP_LEFT.12, KIT1.P$9 (P9)
unnamed: JP_RIGHT.2, KIT1.VU
unnamed: JP_LEFT.11, KIT1.P$10 (P10)
unnamed: JP_RIGHT.3, KIT1.IF-
unnamed: JP_RIGHT.4, KIT1.IF+
unnamed: JP_RIGHT.11, KIT1.P$30 (P30)
unnamed: JP_RIGHT.9, KIT1.D-
unnamed: JP_RIGHT.10, KIT1.D+
unnamed: JP_LEFT.18, KIT1.VB
unnamed: JP_LEFT.17, KIT1.NR
unnamed: JP_LEFT.16, KIT1.P$5 (P5)
unnamed: JP_LEFT.10, KIT1.P$11 (P11)
unnamed: JP_LEFT.9, KIT1.P$12 (P12)
unnamed: JP_LEFT.2, KIT1.P$19 (P19)
unnamed: JP_LEFT.1, KIT1.P$20 (P20)
PULS+: JP_LEFT.15, KIT1.P$6 (P6); also elsewhere on the board
RD+: JP_RIGHT.6, KIT1.RD+; also elsewhere on the board
RD-: JP_RIGHT.5, KIT1.RD-; also elsewhere on the board
SCL: JP_RIGHT.14, KIT1.P$27 (P27); also elsewhere on the board
SDA: JP_RIGHT.13, KIT1.P$28 (P28); also elsewhere on the board
SERVO_ON: JP_LEFT.14, KIT1.P$7 (P7); also elsewhere on the board
SIGN+: JP_RIGHT.15, KIT1.P$26 (P26); also elsewhere on the board
TD+: JP_RIGHT.8, KIT1.TD+; also elsewhere on the board
TD-: JP_RIGHT.7, KIT1.TD-; also elsewhere on the board
VCC: JP_LEFT.19, KIT1.VIN, R16_ALM.2; also elsewhere on the board

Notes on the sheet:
- 24V +
- 5V +
-3V3+
+12V
-12V
NIVELES DE VOLTAJE
MICRORONTROLADOR ARM MBED
